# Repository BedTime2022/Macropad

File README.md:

# Macropad by BedTime thanks to blueprint by Hackclub and AMD !!!!

On 6 of december,
I started designing the macropad, with the intent of 
making a 4 keys keyboard for ddr like games.
after some thought I decided to add a enter and dfjk keys.

# features 

1. DFJK input macropad.

2. Oled showing keys being pressed.

3. 5 leds sk6812mini

4. 5 cherry mx switches 

5. XIAO RP2040 based

![PCB 3d render [1]](Assets/PCB_MODEL_A.png)
![PCB 3d render [2]](Assets/PCB_MODEL_B.png)

![PCB 3d render [3]](Assets/yeii5.png)
![PCB 3d render [4]](Assets/yeii6.png)

# BOM:

- Bill of Materials 

Item	                    	                           

- Cherry MX Switches	Standard mechanical switches	5	

- Blank DSA Keycaps	Profile keycaps compatible with MX switches	5	

- SK6812 Mini LEDs	Addressable RGB LEDs	5	

- Seeed XIAO RP2040	Microcontroller board (RP2040)	1	

- M3×16 Bolts		4	

- M3 Heatset Inserts	Brass inserts for mounting	4	

- PCB Fabrication	from jlcpcb	1	

- 3D Printed Case – Top	Custom enclosure piece	1	

- 3D Printed Case – Bottom	Custom enclosure piece	1	

# CHALLENGES 
I am absolutly new to circuit design and 3d modeling 
and even though the process was really straight 
forward thanks to the tutorial.

Using fusion 360 gave me some headaches for sure.

designing the top model of the case took me 2 days 😭 
it is finally dine and helped me a lot to understand more
what I wanted and notice desing flaws on the pcb.

# Changes for the future

- I would like to setup the current "enter" key to be a 
"change" or "mode" key to change betweent layouts 
(getting dfjk to be arrows for example).

- Getting the Display to show more stuff.
the original idea was to have the display to show the
keys being pressed for aesthethics but also i've been 
thinking about makingit capable of showing information 
from api's.
(like media playing, weather, gif's, etc.)

- I will be updating the repo if any problems are found with either the design or the code used, also images from the product ensambled :3.

THANKS a lot to hackclub and amd for creating 
blueprint check it out at https://blueprint.hackclub.com/. ^^

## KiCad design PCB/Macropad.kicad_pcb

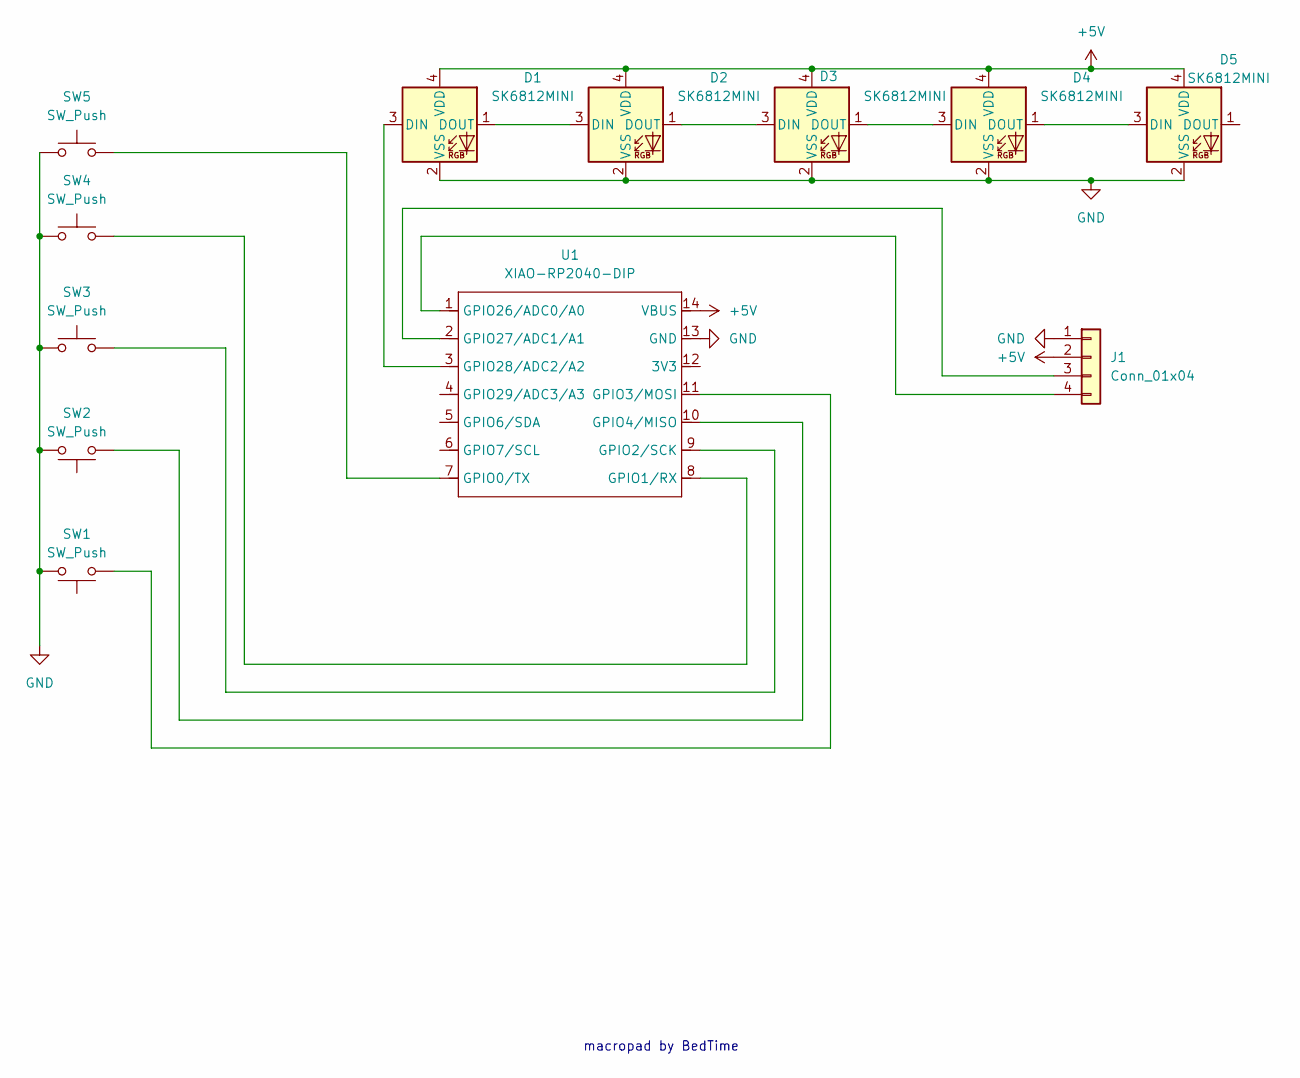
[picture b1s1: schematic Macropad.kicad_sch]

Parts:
D1, D2, D3, D4, D5: SK6812MINI; LED_SK6812MINI_PLCC4_3.5x3.5mm_P1.75mm
J1: Conn_01x04; SSD1306-0.91-OLED-4pin-128x32
SW1, SW2, SW3, SW4, SW5: SW_Push; SW_Cherry_MX_1.00u_PCB
U1: XIAO-RP2040-DIP

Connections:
+5V: D1.4 (VDD), D2.4 (VDD), D3.4 (VDD), D4.4 (VDD), D5.4 (VDD), J1.2, U1.14 (VBUS)
GND: D1.2 (VSS), D2.2 (VSS), D3.2 (VSS), D4.2 (VSS), D5.2 (VSS), J1.1, SW1.2, SW2.2, SW3.1, SW4.1, SW5.1, U1.13 (GND)
unnamed: D1.3 (DIN), U1.3 (GPIO28/ADC2/A2)
unnamed: D1.1 (DOUT), D2.3 (DIN)
unnamed: D2.1 (DOUT), D3.3 (DIN)
unnamed: D3.1 (DOUT), D4.3 (DIN)
unnamed: D4.1 (DOUT), D5.3 (DIN)
unnamed: J1.3, U1.2 (GPIO27/ADC1/A1)
unnamed: J1.4, U1.1 (GPIO26/ADC0/A0)
unnamed: SW5.2, U1.7 (GPIO0/TX)
unnamed: SW4.2, U1.8 (GPIO1/RX)
unnamed: SW3.2, U1.9 (GPIO2/SCK)
unnamed: SW1.1, U1.11 (GPIO3/MOSI)
unnamed: SW2.1, U1.10 (GPIO4/MISO)

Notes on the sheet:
macropad by BedTime

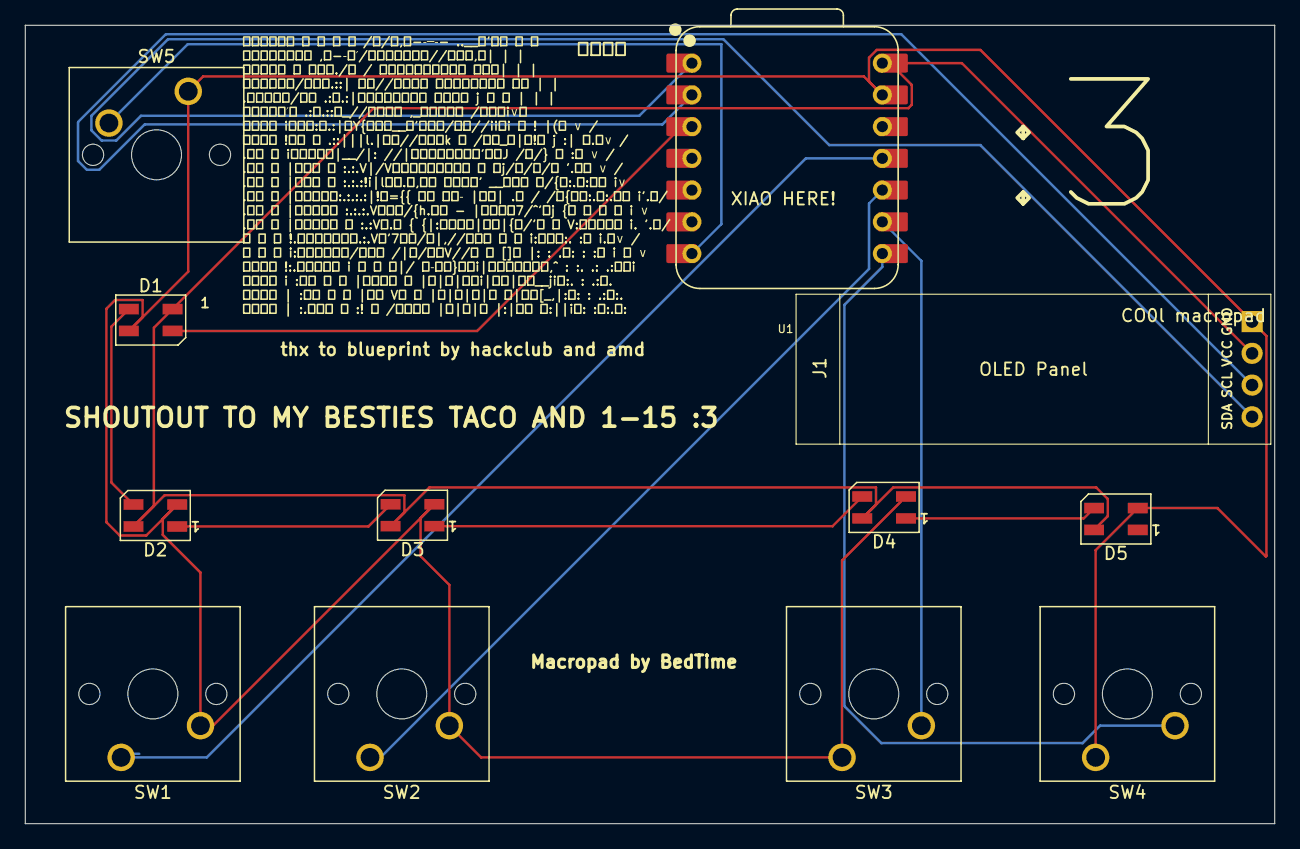
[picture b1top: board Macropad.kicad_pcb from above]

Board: 2 copper layers, 100.0 x 63.9 mm, 12 parts (0 on the bottom side), 14 nets.

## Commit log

2025-12-08 Initiated project with schemmatics and PCB layout.
2025-12-08 Add initial README content for macropad project
    Document the design process and features of the macropad.
2025-12-10 added the libraries!!!
2025-12-10 key caps i think
2025-12-11 the design was too big so I compacted it
2025-12-11 added 3D models of the case
2025-12-11 Organized the files
2025-12-12 3d models
2025-12-12 Readme 1.0
2025-12-12 fixed typo
2025-12-12 updates to the readme
2025-12-13 fixed issue with bom
2025-12-13 typo
2025-12-13 typo again
2025-12-13 added step of the pcb
2025-12-15 Top 3d model was awful and had to remove it, added render of built
2025-12-15 Update README.md
    Changed photos
2025-12-15 Update README.md
    Fixed typo added new entries
2025-12-16 open case images
2025-12-16 new renders
